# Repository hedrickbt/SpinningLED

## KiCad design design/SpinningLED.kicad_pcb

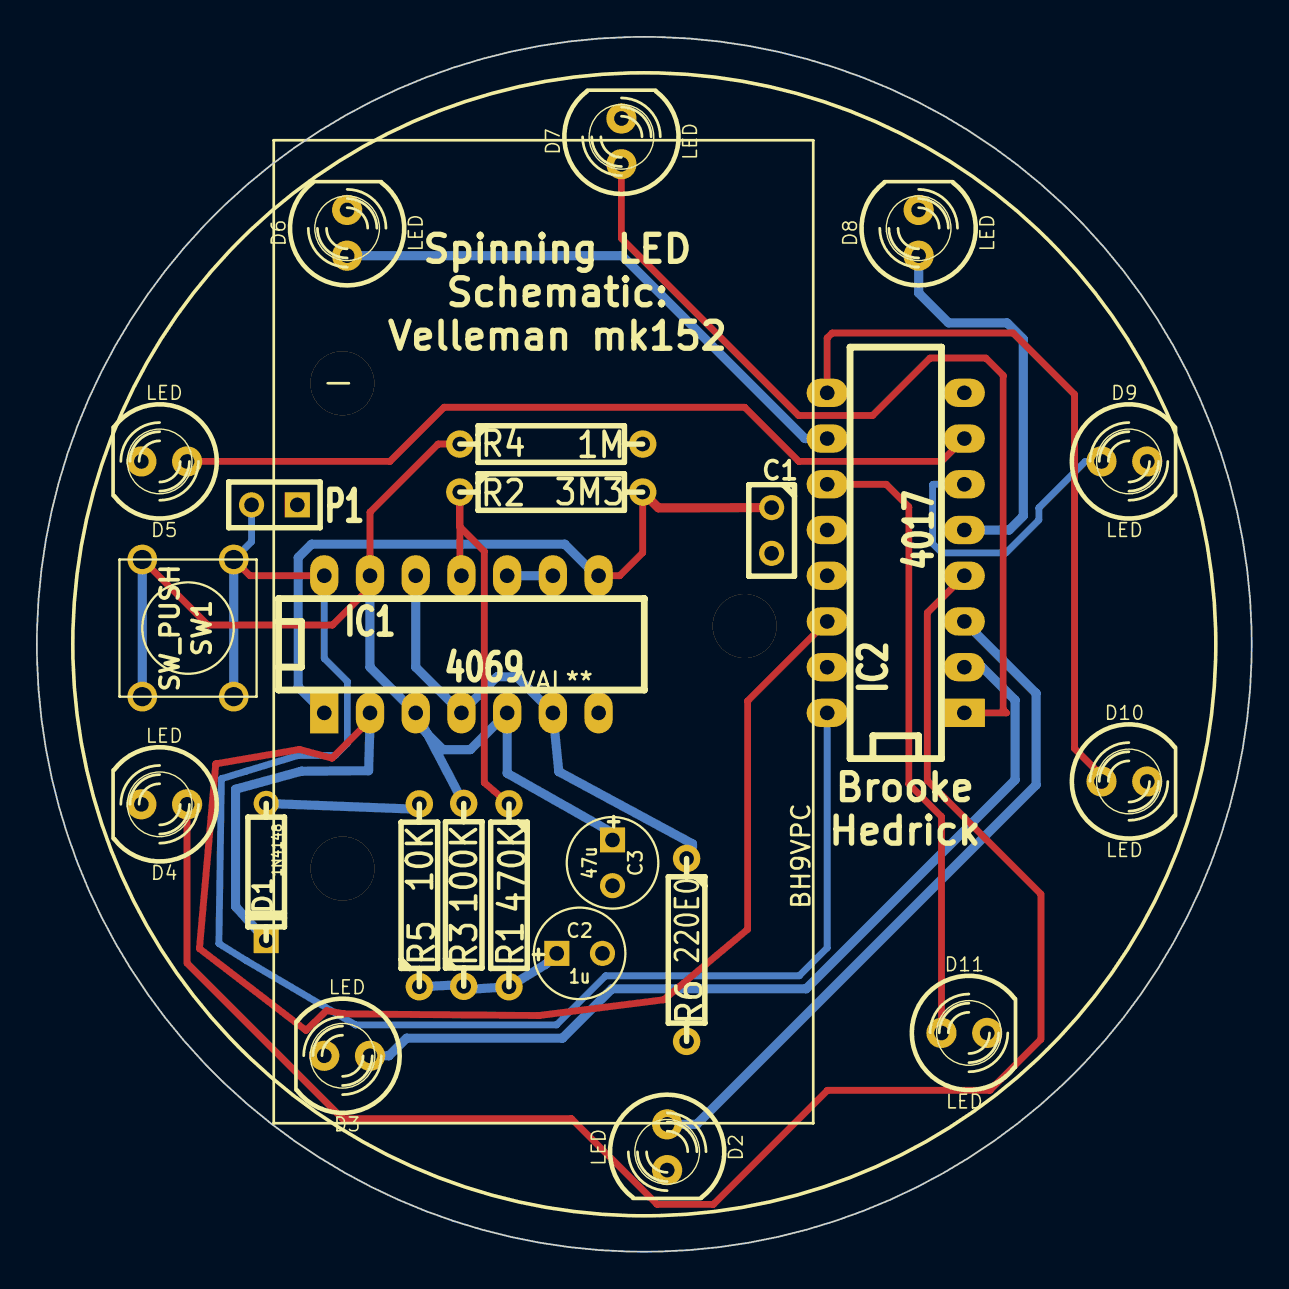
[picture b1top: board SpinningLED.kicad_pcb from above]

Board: 2 copper layers, 67.5 x 67.5 mm, 25 parts (0 on the bottom side), 20 nets.

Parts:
BH9VPC: VAL**; BH9VPC
C1: 10n; C1
C2: 1u; C1V5
C3: 47u; C1V5
D1: 1N4148; D3
D2, D3, D4, D5, D6, D7, D8, D9, D10, D11: LED; LED-5MM
IC1: 4069; DIP-14__300_ELL
IC2: 4017; DIP-16__300_ELL
P1: CONN_2; SIL-2
R1: 470K; R4
R2: 3M3; R4
R3: 100K; R4
R4: 1M; R4
R5: 10K; R4
R6: 220E0; R4
SW1: SW_PUSH; SW_PUSH_SMALL_BTH

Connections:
+9V: C3.1, IC1.3, IC1.5, IC1.13, R3.2, R4.1, SW1.2
GND: C1.2, C2.2, C3.2, D2.2, D3.2, D4.2, D5.2, D6.2, D7.2, D8.2, D9.2, D10.2, D11.2, IC1.7, IC2.8, IC2.13, IC2.15, P1.1, R4.2, R6.2
unnamed: D1.1, R5.2
unnamed: D1.2, IC1.2, IC2.14
unnamed: D6.1, IC2.10
unnamed: D2.1, IC2.3
unnamed: D3.1, IC2.2
unnamed: D4.1, IC2.4
unnamed: D5.1, IC2.7
unnamed: D7.1, IC2.1
unnamed: D8.1, IC2.5
unnamed: D9.1, IC2.6
unnamed: D10.1, IC2.9
unnamed: D11.1, IC2.11
unnamed: C1.1, IC1.1, IC1.8, R2.2
unnamed: IC1.11, R1.1, R2.1
unnamed: IC1.4, IC1.6, IC1.12, R6.1
unnamed: IC1.9, IC1.10
unnamed: C2.1, R1.2, R3.1, R5.1
VCC: IC1.14, IC2.16, P1.2, SW1.1

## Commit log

2013-09-05 Initial
2013-09-08 Routed traces complete
    Also removed R7 - 0 ohm resistor
2013-09-09 V1 ready for OSH Park
2013-10-08 Order updates
2013-10-09 osh park merged drill files
    There was an issues with the NPTH holes being in their own drill file
2013-11-17 SpinningLED v3
